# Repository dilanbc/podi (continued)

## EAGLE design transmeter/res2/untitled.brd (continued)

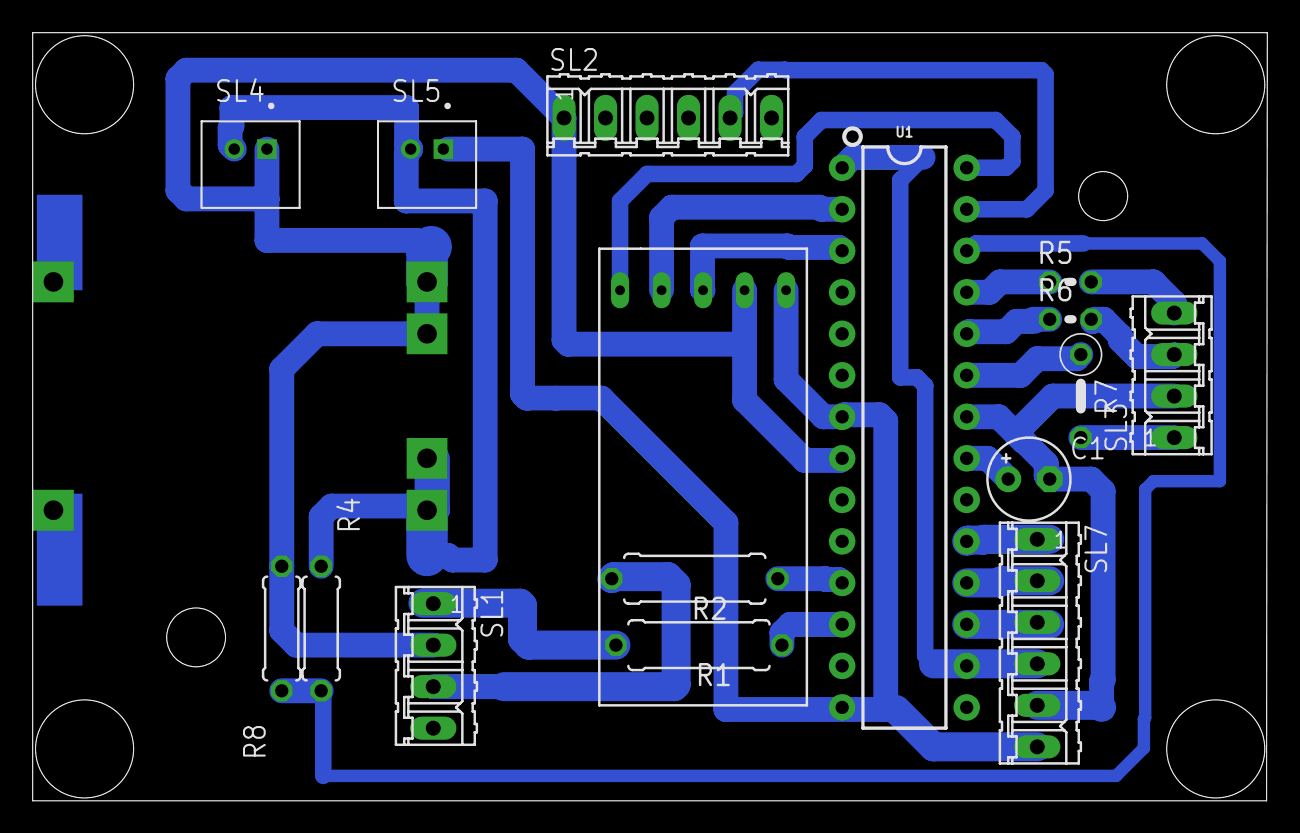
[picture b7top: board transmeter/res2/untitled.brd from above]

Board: 2 copper layers, 75.5 x 47.0 mm, 17 parts (1 on the bottom side), 23 nets.

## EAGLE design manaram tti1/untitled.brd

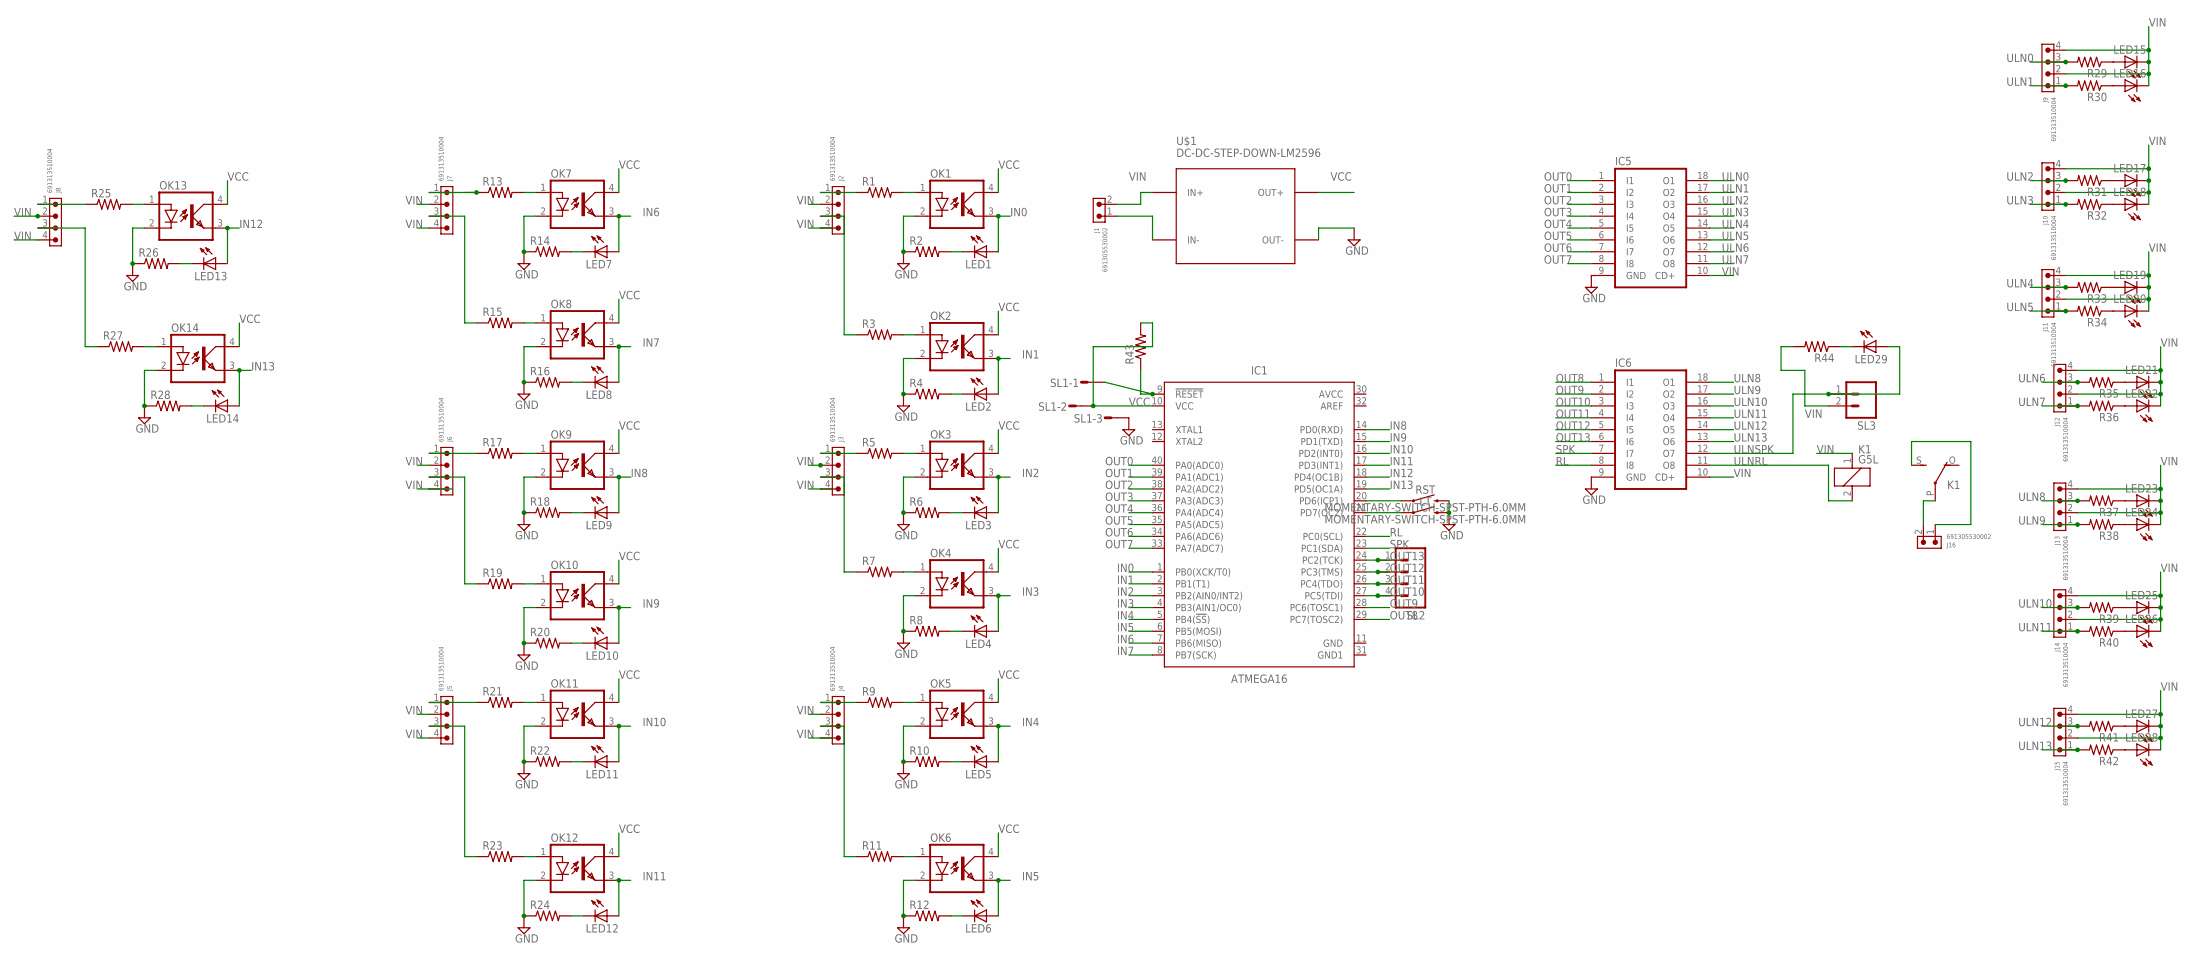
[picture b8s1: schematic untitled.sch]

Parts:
IC1: ATMEGA16; DIP1587W56P254L5229H482Q40B
IC5, IC6: ULN2803A; DIL18
J1, J16: 691305530002
J2, J3, J4, J5, J6, J7, J8, J9, J10, J11, J12, J13, J14, J15: 691313510004
K1: G5L; G5LE
LED1, LED2, LED3, LED4, LED5, LED6, LED7, LED8, LED9, LED10, LED11, LED12, LED13, LED14, LED15, LED16, LED17, LED18, LED19, LED20, LED21, LED22, LED23, LED24, LED25, LED26, LED27, LED28, LED29: LED5MM
LT: MOMENTARY-SWITCH-SPST-PTH-6.0MM; TACTILE_SWITCH_PTH_6.0MM
OK1, OK2, OK3, OK4, OK5, OK6, OK7, OK8, OK9, OK10, OK11, OK12, OK13, OK14: PC817; DIL04
R1, R2, R3, R4, R5, R6, R7, R8, R9, R10, R11, R12, R13, R14, R15, R16, R17, R18, R19, R20, R21, R22, R23, R24, R25, R26, R27, R28, R29, R30, R31, R32, R33, R34, R35, R36, R37, R38, R39, R40, R41, R42, R43, R44: R-US_0207/7; 0207/7
RST: MOMENTARY-SWITCH-SPST-PTH-6.0MM; TACTILE_SWITCH_PTH_6.0MM
SL1: M03S; 03P
SL2: M04; 04P
SL3: M02; 02P
U$1: DC-DC-STEP-DOWN-LM2596

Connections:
AVCC: IC1.30 (AVCC)
GND: IC1.11 (GND), IC5.9 (GND), IC6.9 (GND), LT.3 (2), OK1.2 (C), OK2.2 (C), OK3.2 (C), OK4.2 (C), OK5.2 (C), OK6.2 (C), OK7.2 (C), OK8.2 (C), OK9.2 (C), OK10.2 (C), OK11.2 (C), OK12.2 (C), OK13.2 (C), OK14.2 (C), R2.1, R4.1, R6.1, R8.1, R10.1, R12.1, R14.1, R16.1, R18.1, R20.1, R22.1, R24.1, R26.1, R28.1, RST.3 (2), SL1.3, U$1.OUT-
GND1: IC1.31 (GND1)
IN0: IC1.1 (PB0(XCK/T0)), LED1.A, OK1.3 (EMIT)
IN1: IC1.2 (PB1(T1)), LED2.A, OK2.3 (EMIT)
IN2: IC1.3 (PB2(AIN0/INT2)), LED3.A, OK3.3 (EMIT)
IN3: IC1.4 (PB3(AIN1/OC0)), LED4.A, OK4.3 (EMIT)
IN4: IC1.5 (PB4(!SS!)), LED5.A, OK5.3 (EMIT)
IN5: IC1.6 (PB5(MOSI)), LED6.A, OK6.3 (EMIT)
IN6: IC1.7 (PB6(MISO)), LED7.A, OK7.3 (EMIT)
IN7: IC1.8 (PB7(SCK)), LED8.A, OK8.3 (EMIT)
IN8: IC1.14 (PD0(RXD)), LED9.A, OK9.3 (EMIT)
IN9: IC1.15 (PD1(TXD)), LED10.A, OK10.3 (EMIT)
IN10: IC1.16 (PD2(INT0)), LED11.A, OK11.3 (EMIT)
IN11: IC1.17 (PD3(INT1)), LED12.A, OK12.3 (EMIT)
IN12: IC1.18 (PD4(OC1B)), LED13.A, OK13.3 (EMIT)
IN13: IC1.19 (PD5(OC1A)), LED14.A, OK14.3 (EMIT)
unnamed: J2.1, R1.1
unnamed: OK1.1 (A), R1.2
unnamed: IC1.9 (!RESET!), R43.1, SL1.1
unnamed: LED1.K (C), R2.2
unnamed: J2.3, R3.1
unnamed: OK2.1 (A), R3.2
unnamed: LED17.A, R31.1
unnamed: LED2.K (C), R4.2
unnamed: J3.1, R5.1
unnamed: OK3.1 (A), R5.2
unnamed: LED18.A, R32.1
unnamed: LED3.K (C), R6.2
unnamed: J3.3, R7.1
unnamed: OK4.1 (A), R7.2
unnamed: LED15.A, R29.1
unnamed: LED4.K (C), R8.2
unnamed: J4.1, R9.1
unnamed: OK5.1 (A), R9.2
unnamed: J1.1, U$1.IN-
unnamed: LED19.A, R33.1
unnamed: LED5.K (C), R10.2
unnamed: J4.3, R11.1
unnamed: OK6.1 (A), R11.2
unnamed: LED16.A, R30.1
unnamed: LED6.K (C), R12.2
unnamed: J7.1, R13.1
unnamed: OK7.1 (A), R13.2
unnamed: LED20.A, R34.1
unnamed: LED7.K (C), R14.2
unnamed: J7.3, R15.1
unnamed: OK8.1 (A), R15.2
unnamed: LED21.A, R35.1
unnamed: LED8.K (C), R16.2
unnamed: J6.1, R17.1
unnamed: OK9.1 (A), R17.2
unnamed: LED22.A, R36.1
unnamed: LED9.K (C), R18.2
unnamed: J6.3, R19.1
unnamed: OK10.1 (A), R19.2
unnamed: LED23.A, R37.1
unnamed: LED10.K (C), R20.2
unnamed: J5.1, R21.1
unnamed: OK11.1 (A), R21.2
unnamed: LED24.A, R38.1
unnamed: LED11.K (C), R22.2
unnamed: J5.3, R23.1
unnamed: OK12.1 (A), R23.2
unnamed: LED25.A, R39.1
unnamed: LED12.K (C), R24.2
unnamed: J8.1, R25.1
unnamed: OK13.1 (A), R25.2
unnamed: LED26.A, R40.1
unnamed: LED13.K (C), R26.2
unnamed: J8.3, R27.1
unnamed: OK14.1 (A), R27.2
unnamed: LED27.A, R41.1
unnamed: LED14.K (C), R28.2
unnamed: LED28.A, R42.1
unnamed: IC1.20 (PD6(ICP1)), RST.1
unnamed: IC1.21 (PD7(OC2)), LT.1
unnamed: J16.2, K1.P
unnamed: J16.1, K1.S
unnamed: LED29.K (C), R44.1
OUT0: IC1.40 (PA0(ADC0)), IC5.1 (I1)
OUT1: IC1.39 (PA1(ADC1)), IC5.2 (I2)
OUT2: IC1.38 (PA2(ADC2)), IC5.3 (I3)
OUT3: IC1.37 (PA3(ADC3)), IC5.4 (I4)
OUT4: IC1.36 (PA4(ADC4)), IC5.5 (I5)
OUT5: IC1.35 (PA5(ADC5)), IC5.6 (I6)
OUT6: IC1.34 (PA6(ADC6)), IC5.7 (I7)
OUT7: IC1.33 (PA7(ADC7)), IC5.8 (I8)
OUT8: IC1.29 (PC7(TOSC2)), IC6.1 (I1)
OUT9: IC1.28 (PC6(TOSC1)), IC6.2 (I2)
OUT10: IC1.27 (PC5(TDI)), IC6.3 (I3), SL2.4
OUT11: IC1.26 (PC4(TDO)), IC6.4 (I4), SL2.3
OUT12: IC1.25 (PC3(TMS)), IC6.5 (I5), SL2.2
OUT13: IC1.24 (PC2(TCK)), IC6.6 (I6), SL2.1
RL: IC1.22 (PC0(SCL)), IC6.8 (I8)
SPK: IC1.23 (PC1(SDA)), IC6.7 (I7)
ULN0: IC5.18 (O1), J9.3, R29.2
ULN1: IC5.17 (O2), J9.1, R30.2
ULN2: IC5.16 (O3), J10.3, R31.2
ULN3: IC5.15 (O4), J10.1, R32.2
ULN4: IC5.14 (O5), J11.3, R33.2
ULN5: IC5.13 (O6), J11.1, R34.2
ULN6: IC5.12 (O7), J12.3, R35.2
ULN7: IC5.11 (O8), J12.1, R36.2
ULN8: IC6.18 (O1), J13.3, R37.2
ULN9: IC6.17 (O2), J13.1, R38.2
ULN10: IC6.16 (O3), J14.3, R39.2
ULN11: IC6.15 (O4), J14.1, R40.2
ULN12: IC6.14 (O5), J15.3, R41.2
ULN13: IC6.13 (O6), J15.1, R42.2
ULNRL: IC6.11 (O8), K1.2
ULNSPK: IC6.12 (O7), LED29.A, SL3.1
VCC: IC1.10 (VCC), OK1.4 (COL), OK2.4 (COL), OK3.4 (COL), OK4.4 (COL), OK5.4 (COL), OK6.4 (COL), OK7.4 (COL), OK8.4 (COL), OK9.4 (COL), OK10.4 (COL), OK11.4 (COL), OK12.4 (COL), OK13.4 (COL), OK14.4 (COL), R43.2, SL1.2, U$1.OUT+
VIN: IC5.10 (CD+), IC6.10 (CD+), J1.2, J2.2, J2.4, J3.2, J3.4, J4.2, J4.4, J5.2, J5.4, J6.2, J6.4, J7.2, J7.4, J8.2, J8.4, J9.2, J9.4, J10.2, J10.4, J11.2, J11.4, J12.2, J12.4, J13.2, J13.4, J14.2, J14.4, J15.2, J15.4, K1.1, LED15.K (C), LED16.K (C), LED17.K (C), LED18.K (C), LED19.K (C), LED20.K (C), LED21.K (C), LED22.K (C), LED23.K (C), LED24.K (C), LED25.K (C), LED26.K (C), LED27.K (C), LED28.K (C), R44.2, SL3.2, U$1.IN+

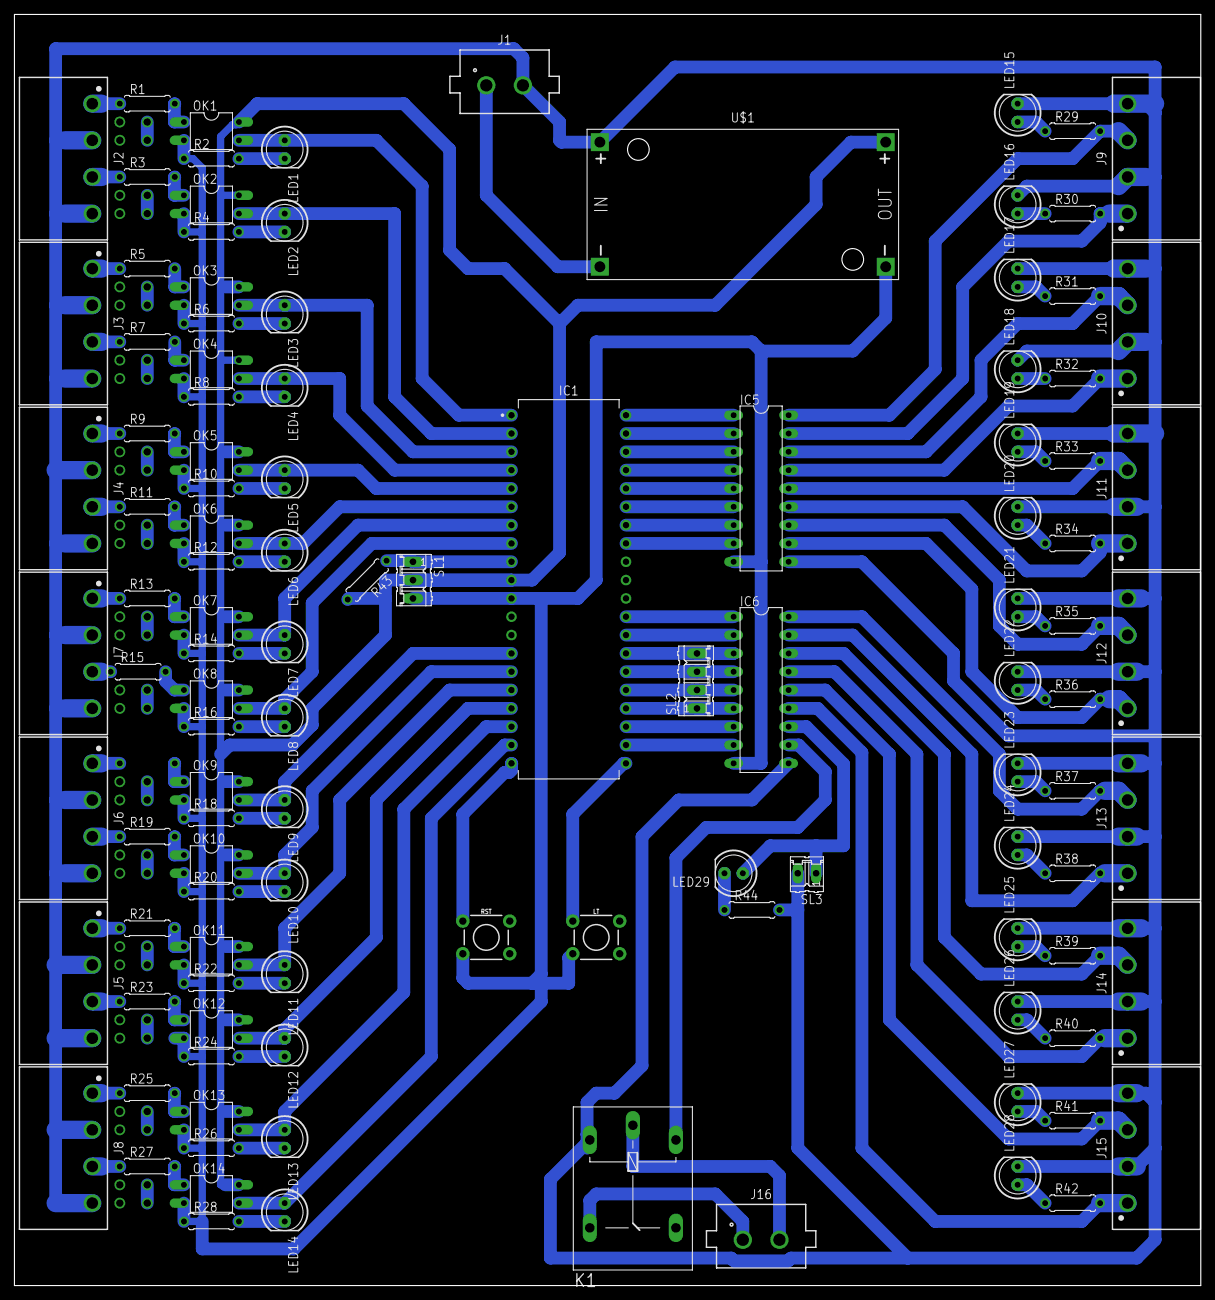
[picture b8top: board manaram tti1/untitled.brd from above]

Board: 2 copper layers, 164.4 x 176.2 mm, 113 parts (1 on the bottom side), 112 nets.
